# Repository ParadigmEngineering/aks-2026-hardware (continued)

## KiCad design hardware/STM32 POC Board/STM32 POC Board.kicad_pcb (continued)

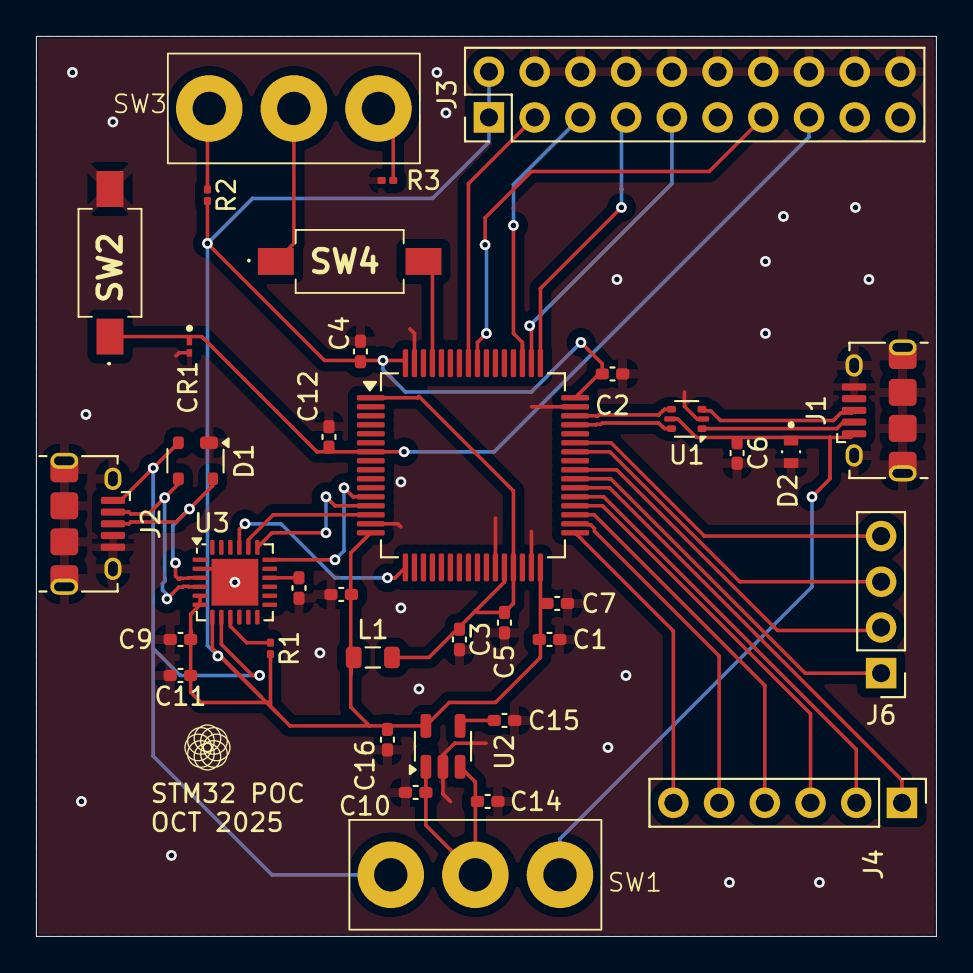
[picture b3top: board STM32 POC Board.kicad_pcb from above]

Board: 4 copper layers, 50.0 x 50.0 mm, 36 parts (0 on the bottom side), 39 nets.

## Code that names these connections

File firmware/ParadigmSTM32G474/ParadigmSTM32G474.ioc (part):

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Mcu.Name=STM32G474R(B-C-E)Tx
Mcu.Package=LQFP64
Mcu.UserName=STM32G474RETx
PA11.Signal=S_TIM4_CH1
PA12.Signal=S_TIM4_CH2
PA13.Mode=Serial_Wire
PA13.Signal=SYS_JTMS-SWDIO
PA14.Mode=Serial_Wire
PA14.Signal=SYS_JTCK-SWCLK
PA2.Mode=Asynchronous
PA2.Signal=LPUART1_TX
PA3.Mode=Asynchronous
PA3.Signal=LPUART1_RX
PA5.Signal=GPIO_Output
PA8.GPIOParameters=GPIO_Label
PA8.GPIO_Label=Steering_Output_B
PA8.Signal=S_TIM1_CH1
PA9.GPIOParameters=GPIO_Label
PA9.GPIO_Label=TIM2_CH3 (ustop)
PA9.Signal=S_TIM2_CH3
PB11.GPIOParameters=GPIO_Label
PB11.GPIO_Label=TIM2_CH4 (Autonomous)
PB11.Signal=S_TIM2_CH4
PB12.Signal=GPIO_Output
PB13.Signal=SPI2_SCK
PB14.Signal=S_TIM15_CH1
PB5.Mode=FDCAN_Activate
PB5.Signal=FDCAN2_RX
PB6.Mode=FDCAN_Activate
PB6.Signal=FDCAN2_TX
PC1.Signal=GPIO_Output
PC6.GPIOParameters=GPIO_Label
PC6.GPIO_Label=Braking1
PC6.Signal=S_TIM8_CH1
PC7.GPIOParameters=GPIO_Label
PC7.GPIO_Label=Braking2
PC7.Signal=S_TIM8_CH2
PC8.Signal=S_TIM3_CH3
PC9.Signal=S_TIM3_CH4
PF0-OSC_IN.Mode=HSE-External-Oscillator
PF0-OSC_IN.Signal=RCC_OSC_IN
PF1-OSC_OUT.Mode=HSE-External-Oscillator
PF1-OSC_OUT.Signal=RCC_OSC_OUT
RCC.HSE_VALUE=16000000
RCC.SYSCLKFreq_VALUE=16000000
board=custom

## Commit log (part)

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2025-09-02 Initial
2025-09-03 ESD for Direct USB. Fixed cursed GND on CP2104
2025-09-16 THIS IS JASONS FAULT
2025-09-28 small tweaks to Fatih changes. Power for CP2104
2025-09-29 This is a commit message
2025-10-07 updated pcb with JTAG and nrst mapped
    Added (copied) schematic for nrst and added JTAG
2025-10-08 created README.md
2025-10-08 added giant Hello World for fun
2025-10-09 Added VDDA, VREF, VBAT. All that is left is I/O pins
2025-10-09 Started layout, footprints will be updated based on component availability
2025-10-12 Whoever made the ESD diodes is a moron. This sucks
2025-10-14 Finished Boot0 circuit and got layout semi done
2025-10-14 Layout mostly done. Fatih's gonna touch it
2025-10-15 Initial layout finished. Not very good, but will get revised
2025-10-15 First rev of STM POC Board. Not great but will be revised
2025-10-20 New revised layout, fixed issues
2025-11-02 Create firmware and hardware folders and add aks-2026-communication-diagram
2025-11-04 Final board
2025-11-12 Add STM32CubeIDE project with custom UART test driver
2025-12-03 Add empty custom FDCAN driver files
2025-12-03 Update fdcan_test.h with function prototypes
2025-12-28 Update UART driver GPIO Moder and AFR register write. Changed configs to CubeIDE project
2025-12-28 Fix: added UART loopback test into User Code section for main.c
2025-12-30 Added ring buffer and RX interrupt for UART test driver
2025-12-31 First rev of 26 aux board
    May need to reroute 48-24 caps, shrink overall size of board
2026-01-01 Update software architecture diagram
2026-01-03 Aux board with integrated FET Bucks
    First rough rev of layout, needs to be refined
2026-01-27 Fix: add CAN configuration
2026-01-27 Fix: add drive_can header and source file
2026-01-28 Fix: added MCU error flags for drive
2026-01-29 Fix: add MCU status and VCU command
2026-02-04 Fix: cleaned up drive header and add drive initialization
2026-02-06 Fix: cleaned up Drive_Init
2026-02-10 Add Send_Handshake command
2026-02-13 Fix: spelling for Drive_SendHandshake
2026-02-25 Cleaned up drive_can header and source
2026-02-25 Add Drive_SendCommand and helper functions
2026-02-26 Add Drive_SendHandshake test to main
2026-03-03 Add more test code for drive
2026-03-06 Add fake mcu for CAN testing
2026-03-06 Add drive CAN testing with other MCU
2026-03-16 Add throttle and e-stop test with RC
2026-03-17 Add capped throttle value
2026-03-18 Add working e-stop
2026-04-09 Add FDCAN interrupt callbacks
2026-04-09 Add remote e-stop with drive
2026-04-09 Add negative current for reverse drive direction
2026-04-21 Add updated steering module based off of main branch
2026-04-25 Update steering for Control Board
2026-04-28 Add braking actuator servo control (STM32G474)
2026-04-28 import braking changes (TIM8 = BRAKING MOTOR)
2026-04-29 Add UART communication with Jetson
2026-05-02 Add reworking drive control
2026-05-02 Add Control Board
2026-05-07 fix braking code, added second servo motor
2026-05-07 metadata idk
2026-05-10 Fix e-stop and increase drive RPM
2026-05-12 Add working remote e-stop
2026-05-16 Fix e-stop braking
2026-05-16 Update software architecture diagram for documentation
2026-05-19 Add urgent stop
2026-05-19 Fix: check ustopped variable for urgent stop
2026-05-19 Add control board final version files
2026-05-20 Fix: RC inputs with new flight controller firmware
